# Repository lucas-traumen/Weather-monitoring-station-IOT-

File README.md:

# Local Weather Monitoring Station

A local weather station for sites where a regional forecast does not describe the microclimate at the sensor. An STM32 node measures the environment, encrypts the reading, and sends it over LoRa. An ESP32-S3 gateway decrypts it, forecasts the temperature two hours ahead, and stores the result in Supabase.

**Team:** Nguyễn Thái Anh (23139002), Lê Đức Trí (23139049)
**Supervisor:** Dr. Huỳnh Thế Thiện, HCMC University of Technology and Education
**Report:** [report/23139002_23139049.pdf](report/23139002_23139049.pdf)

## What it does

Regional stations miss differences caused by vegetation, concrete, elevation, and shielding. This station measures temperature, humidity, pressure, and supply status at the installation point, then keeps that record available when the gateway has Wi-Fi.

*Figure 2.1. System architecture. Sensing at 433 MHz, gateway at the edge, application tier over HTTPS.*

| Tier | Role |
| --- | --- |
| STM32F103C8T6 node | Read SHT30, BMP388, and INA219; pack a 10-byte payload; encrypt it; transmit one LoRa frame per cycle |
| ESP32-S3 gateway | Authenticate and decrypt the frame, run the forecast, re-encrypt, and POST to Supabase |
| Supabase | Decrypt in an Edge Function, store rows in PostgreSQL, and serve the dashboard and OTA metadata |

The outdoor link uses ASCON-128a with a 4-byte authentication tag so the frame stays small. The gateway-to-cloud link uses a second key and a 16-byte tag. A leaked LoRa key does not expose the cloud key.

## Run the dashboard

The dashboard is static HTML. It reads rows that the Edge Function has already decrypted.

```bash
cd Software/iot-dashboard
python3 -m http.server 8080
```

Open `http://localhost:8080`. In **Config**, set the Supabase URL and table (`weather_logs`). The browser does not hold the ASCON key.

## Build the firmware

**Gateway** — ESP-IDF project `esp32_gateway`, target ESP32-S3. The managed provisioning component supports ESP-IDF 5.1 through 5.5 and 6.x; use an installed 5.x toolchain unless you have confirmed 6.x.

```bash
cd firmware/esp32
idf.py set-target esp32s3
idf.py build flash monitor
```

**Sensor node** — STM32CubeIDE project generated with STM32CubeMX 6.14.1 and STM32Cube FW_F1 V1.8.7.

```bash
# Open firmware/stm32/node_stm32_ver1 in STM32CubeIDE and build the Debug configuration.
```

There is no top-level Makefile for the STM32 tree.

## How the problems were handled

**Payload size on a small MCU.** AES-GCM is a poor fit for the STM32F103 frame budget. ASCON-128a encrypts the 10-byte payload in software. The LoRa frame is 18 bytes, including a 4-byte tag. The gateway checks that tag before it accepts the sample.

**Radio-on time.** The node does not stream. In each cycle it wakes, checks the schedule, reads the sensors, packs and encrypts the payload, sends one E32 frame at 433 MHz, and returns to standby. Sensors are SHT30, BMP388, and INA219 on I2C. The firmware uses GPIO, UART, RTC, and the independent watchdog.

**Forecast without an external weather API.** The gateway runs a multiple linear regression on temperature, humidity, pressure, and cyclical time features. It writes `predicted_temp_2h` locally. Section 5 gives the error on the deployed model.

**Field updates.** The dashboard hashes the `.bin` with SHA-256, uploads it to the `firmware` bucket, and writes `ota_url`, `ota_seq`, and `ota_sha256` in `device_configs`. The gateway downloads a new sequence, checks the digest, and skips a sequence it has already applied.

**No self-hosted server.** Supabase provides PostgreSQL, Realtime, Storage, and the Edge Function. The browser only sees plaintext that the function has already written.

## Hardware

The node is an STM32F103C8T6 board in a vented enclosure, charged from two solar panels through a CN3791 and a 1S lithium protection circuit.

*Assembled sensor node (Figure 4.3 in the report).*

The gateway is an ESP32-S3 N16R8 (16 MB flash, 8 MB PSRAM) with a LoRa E32 module on UART. PSRAM holds the TLS buffers and the regression coefficients.

*Assembled gateway (Figure 4.6 in the report).*

## Results

Evaluation used the deployed system, not a separate simulation. Details and plots are in Chapter 5 of the report.

**HTTPS latency** (Table 5.1), three trials:

| Path | Mean |
| --- | ---: |
| ESP32-S3 to Supabase Edge Function | 4595 ms |
| Web dashboard query to Supabase | 160 ms |

The gateway figure is the time from the start of the HTTPS request until the Edge Function responds, measured on the device. It moves with Wi-Fi and Edge Function load. The dashboard figure is the browser query, not the ingest path.

**ASCON.** The gateway rejects frames whose 4-byte tag does not match. Tampered frames do not enter the database.

**Forecast** (Table 5.2), 1755 paired samples from 13 June 2026 through 28 June 2026:

| Samples | MAE | RMSE | R² | Bias (actual − predicted) |
| ---: | ---: | ---: | ---: | ---: |
| 1755 | 1.84 °C | 2.79 °C | 0.771 | +0.62 °C |

The positive bias means the model tends to forecast low. Error is smaller at night, when temperature changes slowly, and larger between about 10:00 and 15:00. The largest residual in the set is −12.77 °C (forecast 41.10 °C, actual 28.33 °C two hours later, 16 June 2026, 13:00).

*Predicted temperature and the temperature measured two hours later (Figure 5.18).*

*Predicted versus actual temperature. The dashed line is y = x (Figure 5.19).*

*Forecast error over the evaluation window (Figure 5.20).*

**OTA.** Upload from the dashboard, SHA-256 check on the gateway, and flash completed. A repeated sequence number was ignored.

## Repository layout

```
firmware/esp32/     ESP-IDF gateway (FreeRTOS tasks, ASCON, LoRa, MLR)
firmware/stm32/     STM32CubeIDE sensor-node project
Software/iot-dashboard/   Static dashboard (index.html, chart.html)
Hardware/           Schematics and PCB
docs/images/        Figures cropped from the report
report/             Full report (PDF)
```

## Limits

- One sensor node and one gateway were deployed. The frame format can take more nodes; that load was not measured.
- Outdoor enclosure life (UV, heat cycling, rain) was not tested. Long-term solar autonomy was not optimized.
- The regression is a short-horizon reference. It does not replace a meteorological model, and it misses fast daytime swings. A rate-of-change feature and a longer record are the next step.
- Keys are static. Enrollment, rotation, and device identity are out of scope.
- The AEAD associated data is empty. Device ID, frame type, and a counter can be bound there later.

## References

Cited where the design depends on them:

- Dobraunig, C., Eichlseder, M., Grassi, L., et al. (2021). *ASCON v1.2: Lightweight Authenticated Encryption and Hashing*. NIST Lightweight Cryptography Standardization Process. Used for the AEAD on both links (Sections 3 and 5).
- Semtech Corporation. (2023). *LoRa Modulation Basics*, AN1200.22. Used for the 433 MHz E32 link.
- STMicroelectronics. *RM0008 Reference Manual: STM32F10xxx*. Register and peripheral behavior for the F103 firmware (STM32Cube FW_F1 V1.8.7).
- Espressif Systems. *ESP32-S3 Technical Reference Manual* and ESP-IDF programming guide. Gateway tasks, HTTPS, and OTA.
- Supabase. *Realtime, Storage, and Edge Functions*. https://supabase.com/docs. Cloud ingest, dashboard reads, and firmware hosting.

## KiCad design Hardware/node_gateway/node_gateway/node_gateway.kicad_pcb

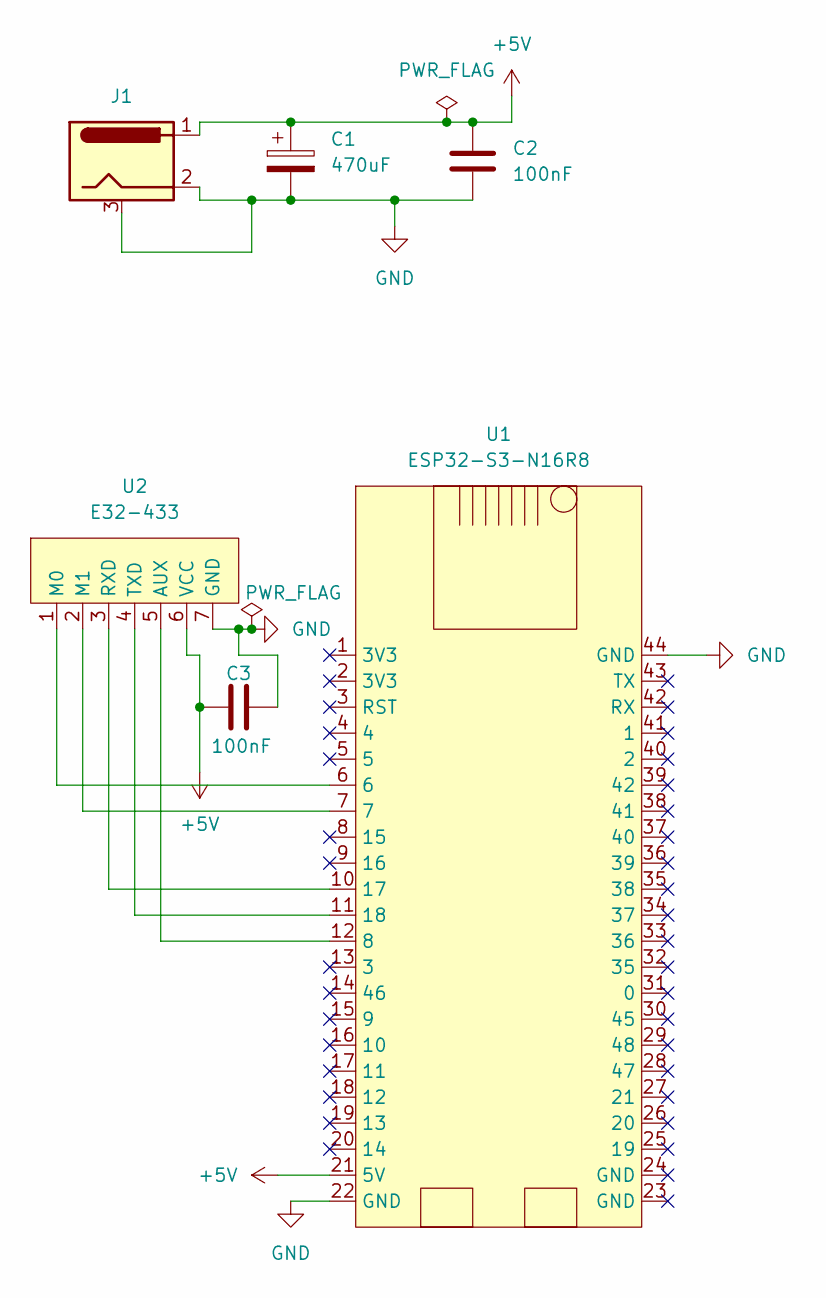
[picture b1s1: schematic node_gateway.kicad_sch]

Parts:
C1: 470uF; CP_Radial_D8.0mm_P3.0mm
C2, C3: 100nF; C_Disc_D5.0mm_W2.5mm_P5.00mm
J1: Conn_Jack-DC; BarrelJack_GCT_DCJ200-10-A_Horizontal
U1: ESP32-S3-N16R8
U2: E32-433; PinSocket_1x07_P2.54mm_Vertical

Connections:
+5V: C1.1, C2.1, C3.2, J1.1, U1.21 (5V), U2.6 (VCC)
GND: C1.2, C2.2, C3.1, J1.2, J1.3, U1.22 (GND), U1.44 (GND), U2.7 (GND)
unnamed: U1.12 (8), U2.5 (AUX)
unnamed: U1.10 (17), U2.3 (RXD)
unnamed: U1.11 (18), U2.4 (TXD)
unnamed: U1.6, U2.1 (M0)
unnamed: U1.7, U2.2 (M1)

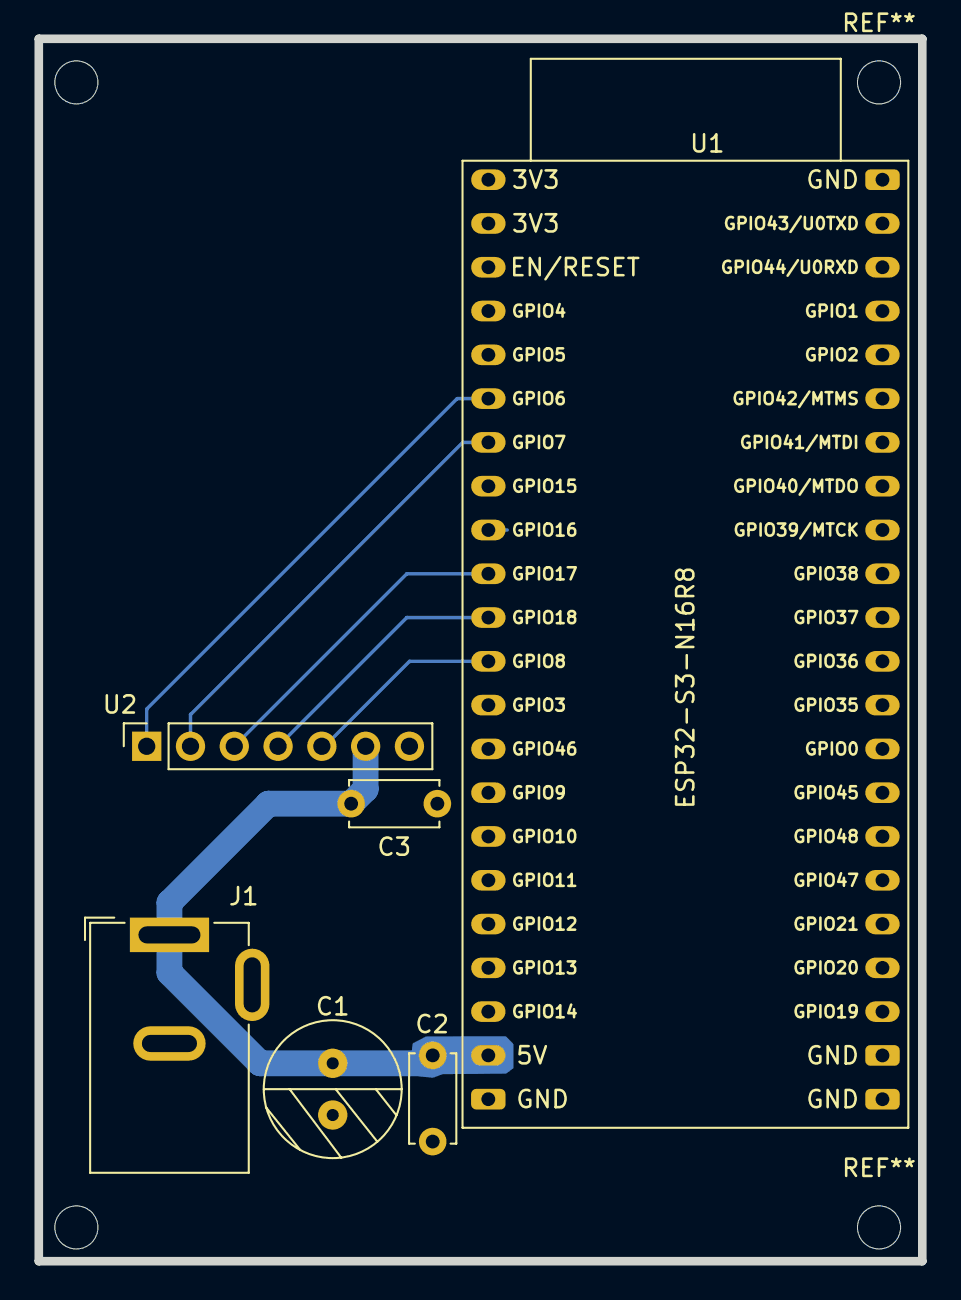
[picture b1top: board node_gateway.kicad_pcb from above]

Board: 2 copper layers, 51.3 x 70.9 mm, 6 parts (0 on the bottom side), 7 nets.

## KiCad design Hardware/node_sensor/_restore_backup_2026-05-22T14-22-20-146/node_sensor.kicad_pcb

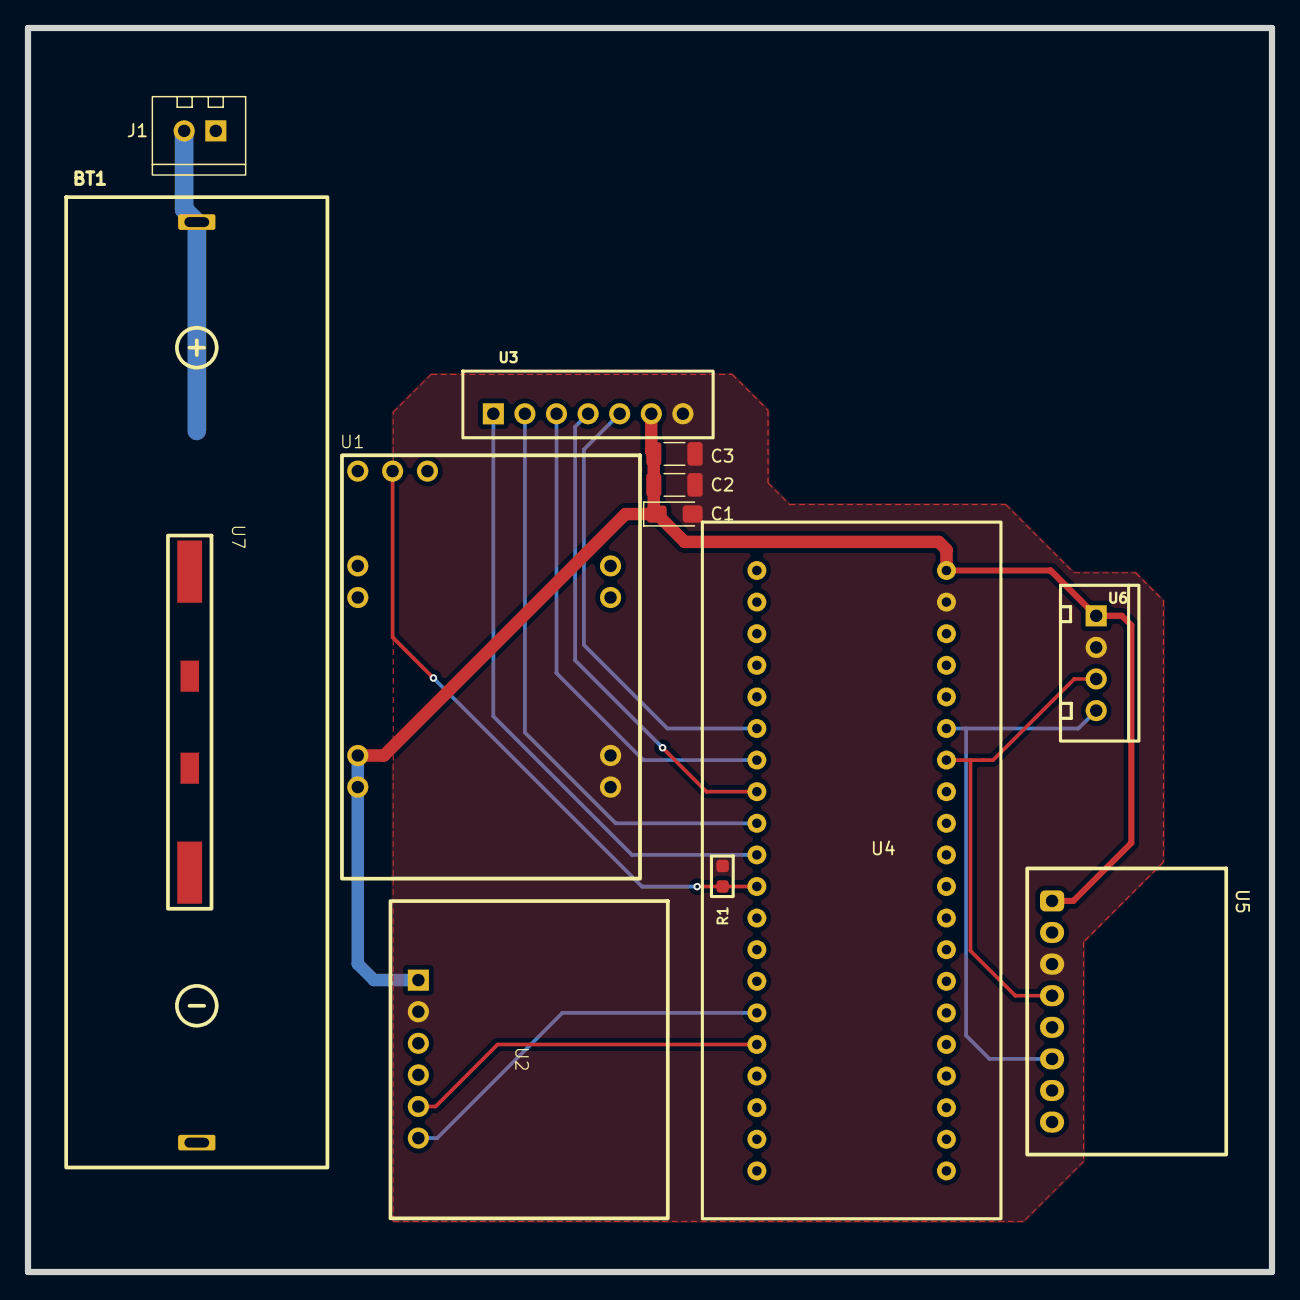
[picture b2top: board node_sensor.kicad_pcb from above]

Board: 2 copper layers, 100.0 x 100.0 mm, 13 parts (0 on the bottom side), 14 nets.

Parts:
BT1: Battery_Cell; Battery-18560-1s
C1: 100uF; CP_EIA-3216-18_Kemet-A_HandSolder
C2: 0.1uF; L_1206_3216Metric_Pad1.22x1.90mm_HandSolder
C3: 0.1nF; L_1206_3216Metric_Pad1.22x1.90mm_HandSolder
J1: Solar_Pannel; XH 2.54 2Pin Female
R1: 10k; R0603
U1: TPS63020; TPS63020-module
U2: INA219
U3: E32-433; Conn_XH-P2.54mm-7P
U4: DevKitSTM32
U5: BMP-388; BMP388-module
U6: SHT30; Conn_XH-P2.54mm-4P
U7: BMS-1s; BMS-1s-18560

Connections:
+3.3V: C1.1, C2.1, C3.1, U1.7 (VOUT), U2.1 (VCC), U3.6 (VCC), U4.21 (3v3), U5.1 (VIN), U6.1 (VCC)
/PA1: U3.5 (AUX), U4.6 (PA1)
/PA2: U3.3 (RXD), U4.7 (PA2)
/PA3: U3.4 (TXD), U4.8 (PA3)
/PA4: U3.2 (M1), U4.9 (PA4)
/PA5: U3.1 (M0), U4.10 (PA5)
/PA6: R1.2, U1.4 (PS/SYNC), U4.11 (PA6)
/PB6: U4.27 (PB6), U5.4 (SCK), U6.3 (SCL)
/PB7: U4.26 (PB7), U5.6 (SDI), U6.4 (SDA)
/PB10: U2.6 (SCL), U4.15 (PB10)
/PB11: U2.5 (SDA), U4.16 (PB11)
/Pin+: BT1.1 (+), J1.2, U1.1 (VIN), U1.3 (EN), U2.3 (VIN-), U7.1 (B+)
/Pin-: BT1.2 (-), J1.1, U1.2 (GND), U2.4 (VIN+), U7.2 (B-)
GND: C1.2, C2.2, C3.2, R1.1, U1.6 (GND), U2.2 (GND), U3.7 (GND), U4.22 (GND), U5.3 (GND), U6.2 (GND)

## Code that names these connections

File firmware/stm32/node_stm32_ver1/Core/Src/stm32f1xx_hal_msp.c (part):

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
    __HAL_RCC_GPIOB_CLK_ENABLE();
    /**I2C1 GPIO Configuration
    PB6     ------> I2C1_SCL
    PB7     ------> I2C1_SDA
    */
    GPIO_InitStruct.Pin = ENV_SCL_Pin|ENV_SDA_Pin;
    GPIO_InitStruct.Mode = GPIO_MODE_AF_OD;
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
    __HAL_RCC_GPIOB_CLK_ENABLE();
    /**I2C2 GPIO Configuration
    PB10     ------> I2C2_SCL
    PB11     ------> I2C2_SDA
    */
    GPIO_InitStruct.Pin = SOURCE_SCL_Pin|SOURCE_SDA_Pin;
    GPIO_InitStruct.Mode = GPIO_MODE_AF_OD;
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    __HAL_RCC_I2C1_CLK_DISABLE();

    /**I2C1 GPIO Configuration
    PB6     ------> I2C1_SCL
    PB7     ------> I2C1_SDA
    */
    HAL_GPIO_DeInit(ENV_SCL_GPIO_Port, ENV_SCL_Pin);

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    __HAL_RCC_I2C2_CLK_DISABLE();

    /**I2C2 GPIO Configuration
    PB10     ------> I2C2_SCL
    PB11     ------> I2C2_SDA
    */
    HAL_GPIO_DeInit(SOURCE_SCL_GPIO_Port, SOURCE_SCL_Pin);

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
    __HAL_RCC_GPIOA_CLK_ENABLE();
    /**USART2 GPIO Configuration
    PA2     ------> USART2_TX
    PA3     ------> USART2_RX
    */
    GPIO_InitStruct.Pin = LORA_TX_Pin;
    GPIO_InitStruct.Mode = GPIO_MODE_AF_PP;
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    __HAL_RCC_USART2_CLK_DISABLE();

    /**USART2 GPIO Configuration
    PA2     ------> USART2_TX
    PA3     ------> USART2_RX
    */
    HAL_GPIO_DeInit(GPIOA, LORA_TX_Pin|LORA_RX_Pin);

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
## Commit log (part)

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2026-03-22 firmware stm32
2026-03-24 min-filter
2026-04-17 lora +rtc+iwdg
2026-04-22 add lora.h
2026-04-24 debug lora
2026-04-27 test lora v1.2
2026-04-27 fixed lora v1.1
2026-04-27 testing rtc,IWDG
2026-04-27 board stm32 v1
2026-04-28 deepsleep with 2 bytes frame counter
2026-04-28 stm32 deepsleep+esp32 decode
2026-05-07 completed node_sensor v1.1
2026-05-07 deleted backup
2026-05-07 app/web/DB -> Software
2026-05-15 DB + web
2026-05-15 Update web and database components
2026-05-15 change toolchain to ubuntu
2026-05-15 Bỏ theo dõi các file đã được thêm vào .gitignore
2026-05-17 updated OTA,https
2026-05-17 branch app/DB
2026-05-17 Fix merge conflicts and remove build artifacts from tracking
2026-05-17 Fix merge conflicts and ignore ESP32 build artifacts
2026-05-17 ina219 - 19bytes ascon
2026-05-20 fix ntp - ota- tls
2026-05-20 updated anti-lockup i2c bus feature
2026-05-20 updated web v2.0
2026-05-22 completed v1 node sensor
2026-05-22 queue data buffer
2026-05-22 ML-clean code
2026-05-31 pcb v1 gateway - change mappping gateway
2026-06-06 add en-descypt by edge function in DB
2026-06-15 updated firmware-web-stm32(test)

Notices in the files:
firmware/stm32/node_stm32_ver1/Core/Src/stm32f1xx_hal_msp.c:
Copyright (c) 2026 STMicroelectronics.
All rights reserved.
This software is licensed under terms that can be found in the LICENSE file
